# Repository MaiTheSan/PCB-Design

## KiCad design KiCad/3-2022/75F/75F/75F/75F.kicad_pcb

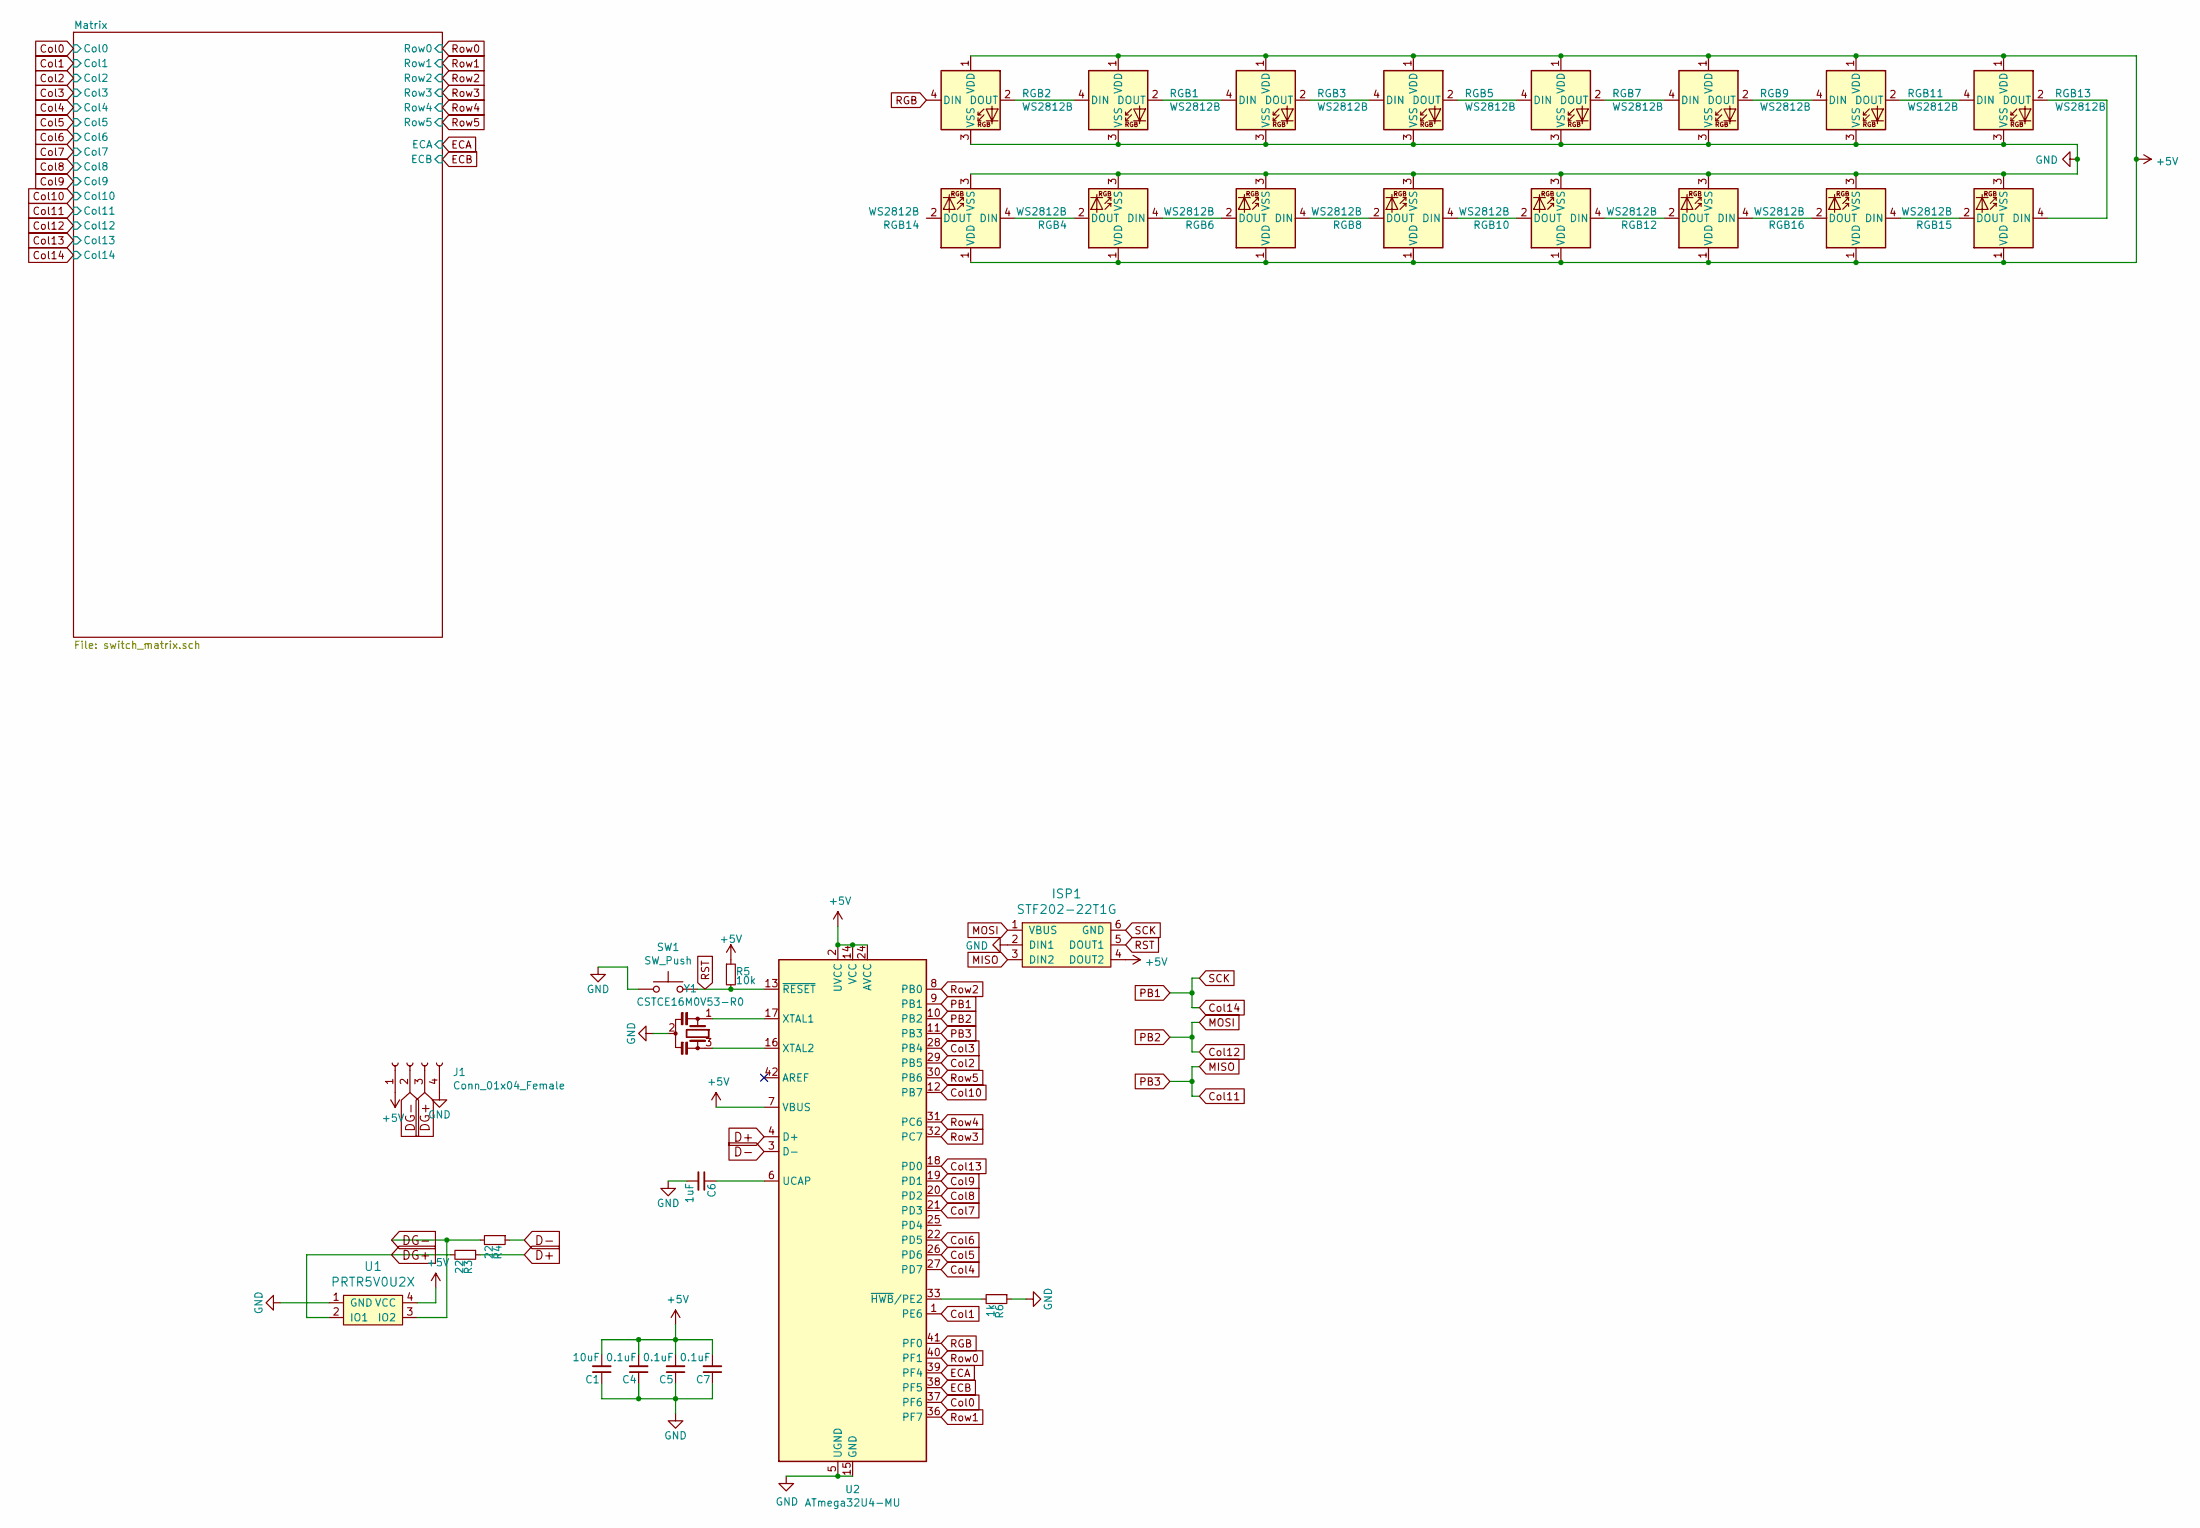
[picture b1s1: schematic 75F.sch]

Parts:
C1: 10uF; C_0603
C4, C5, C7: 0.1uF; C_0603
C6: 1uF; C_0603
ISP1: STF202-22T1G; Tag-Connect_TC2030-IDC-NL_2x03_P1.27mm_Vertical
J1: Conn_01x04_Female; JST-SR-4
R3, R4: 22; R_0805
R5: 10k; R_0805
R6: 1k; R_0805
RGB1, RGB2, RGB3, RGB4, RGB5, RGB6, RGB7, RGB8, RGB9, RGB10, RGB11, RGB12, RGB13, RGB15, RGB16: WS2812B; LED_WS2812B_PLCC4_5.0x5.0mm_P3.2mm
RGB14: WS2812B; RGB-6028_FLIPPED
SW1: SW_Push; SKQG-1155865
U1: PRTR5V0U2X; SOT143B
U2: ATmega32U4-MU; QFN-44-1EP_7x7mm_P0.5mm_EP5.15x5.15mm
Y1: CSTCE16M0V53-R0; Resonator_SMD_muRata_CSTxExxV-3Pin_3.0x1.1mm

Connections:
+5V: C1.2, C4.2, C5.2, C7.2, ISP1.4 (DOUT2), J1.1, R5.1, RGB1.1 (VDD), RGB2.1 (VDD), RGB3.1 (VDD), RGB4.1 (VDD), RGB5.1 (VDD), RGB6.1 (VDD), RGB7.1 (VDD), RGB8.1 (VDD), RGB9.1 (VDD), RGB10.1 (VDD), RGB11.1 (VDD), RGB12.1 (VDD), RGB13.1 (VDD), RGB14.1 (VDD), RGB15.1 (VDD), RGB16.1 (VDD), U1.4 (VCC), U2.2 (UVCC), U2.7 (VBUS), U2.14 (VCC), U2.24 (AVCC), U2.34 (VCC), U2.44 (AVCC); also elsewhere on the board
Col0: U2.37 (PF6); also elsewhere on the board
Col1: U2.1 (PE6); also elsewhere on the board
Col2: U2.29 (PB5); also elsewhere on the board
Col3: U2.28 (PB4); also elsewhere on the board
Col4: U2.27 (PD7); also elsewhere on the board
Col5: U2.26 (PD6); also elsewhere on the board
Col6: U2.22 (PD5); also elsewhere on the board
Col7: U2.21 (PD3); also elsewhere on the board
Col8: U2.20 (PD2); also elsewhere on the board
Col9: U2.19 (PD1); also elsewhere on the board
Col10: U2.12 (PB7); also elsewhere on the board
Col11: ISP1.3 (DIN2), U2.11 (PB3); also elsewhere on the board
Col12: ISP1.1 (VBUS), U2.10 (PB2); also elsewhere on the board
Col13: U2.18 (PD0); also elsewhere on the board
Col14: ISP1.6 (GND), U2.9 (PB1); also elsewhere on the board
D+: R3.1, U2.4 (D+)
D-: R4.1, U2.3 (D-)
DG+: J1.3, R3.2, U1.2 (IO1)
DG-: J1.2, R4.2, U1.3 (IO2)
ECA: U2.39 (PF4); also elsewhere on the board
ECB: U2.38 (PF5); also elsewhere on the board
GND: C1.1, C4.1, C5.1, C6.2, C7.1, ISP1.2 (DIN1), J1.4, R6.1, RGB1.3 (VSS), RGB2.3 (VSS), RGB3.3 (VSS), RGB4.3 (VSS), RGB5.3 (VSS), RGB6.3 (VSS), RGB7.3 (VSS), RGB8.3 (VSS), RGB9.3 (VSS), RGB10.3 (VSS), RGB11.3 (VSS), RGB12.3 (VSS), RGB13.3 (VSS), RGB14.3 (VSS), RGB15.3 (VSS), RGB16.3 (VSS), SW1.1, U1.1 (GND), U2.5 (UGND), U2.15 (GND), U2.23 (GND), U2.35 (GND), U2.43 (GND), U2.45 (GND), Y1.2; also elsewhere on the board
unnamed: C6.1, U2.6 (UCAP)
unnamed: R6.2, U2.33 (~HWB~/PE2)
unnamed: RGB1.2 (DOUT), RGB3.4 (DIN)
unnamed: RGB1.4 (DIN), RGB2.2 (DOUT)
unnamed: RGB3.2 (DOUT), RGB5.4 (DIN)
unnamed: RGB4.4 (DIN), RGB6.2 (DOUT)
unnamed: RGB5.2 (DOUT), RGB7.4 (DIN)
unnamed: RGB6.4 (DIN), RGB8.2 (DOUT)
unnamed: RGB7.2 (DOUT), RGB9.4 (DIN)
unnamed: RGB8.4 (DIN), RGB10.2 (DOUT)
unnamed: RGB10.4 (DIN), RGB12.2 (DOUT)
unnamed: RGB11.2 (DOUT), RGB13.4 (DIN)
unnamed: RGB9.2 (DOUT), RGB11.4 (DIN)
unnamed: RGB12.4 (DIN), RGB16.2 (DOUT)
unnamed: RGB13.2 (DOUT), RGB15.4 (DIN)
unnamed: RGB4.2 (DOUT), RGB14.4 (DIN)
unnamed: RGB15.2 (DOUT), RGB16.4 (DIN)
unnamed: U2.16 (XTAL2), Y1.3
unnamed: U2.17 (XTAL1), Y1.1
RGB: RGB2.4 (DIN), U2.41 (PF0)
RST: ISP1.5 (DOUT1), R5.2, SW1.2, U2.13 (~RESET)
Row0: U2.40 (PF1); also elsewhere on the board
Row1: U2.36 (PF7); also elsewhere on the board
Row2: U2.8 (PB0); also elsewhere on the board
Row3: U2.32 (PC7); also elsewhere on the board
Row4: U2.31 (PC6); also elsewhere on the board
Row5: U2.30 (PB6); also elsewhere on the board

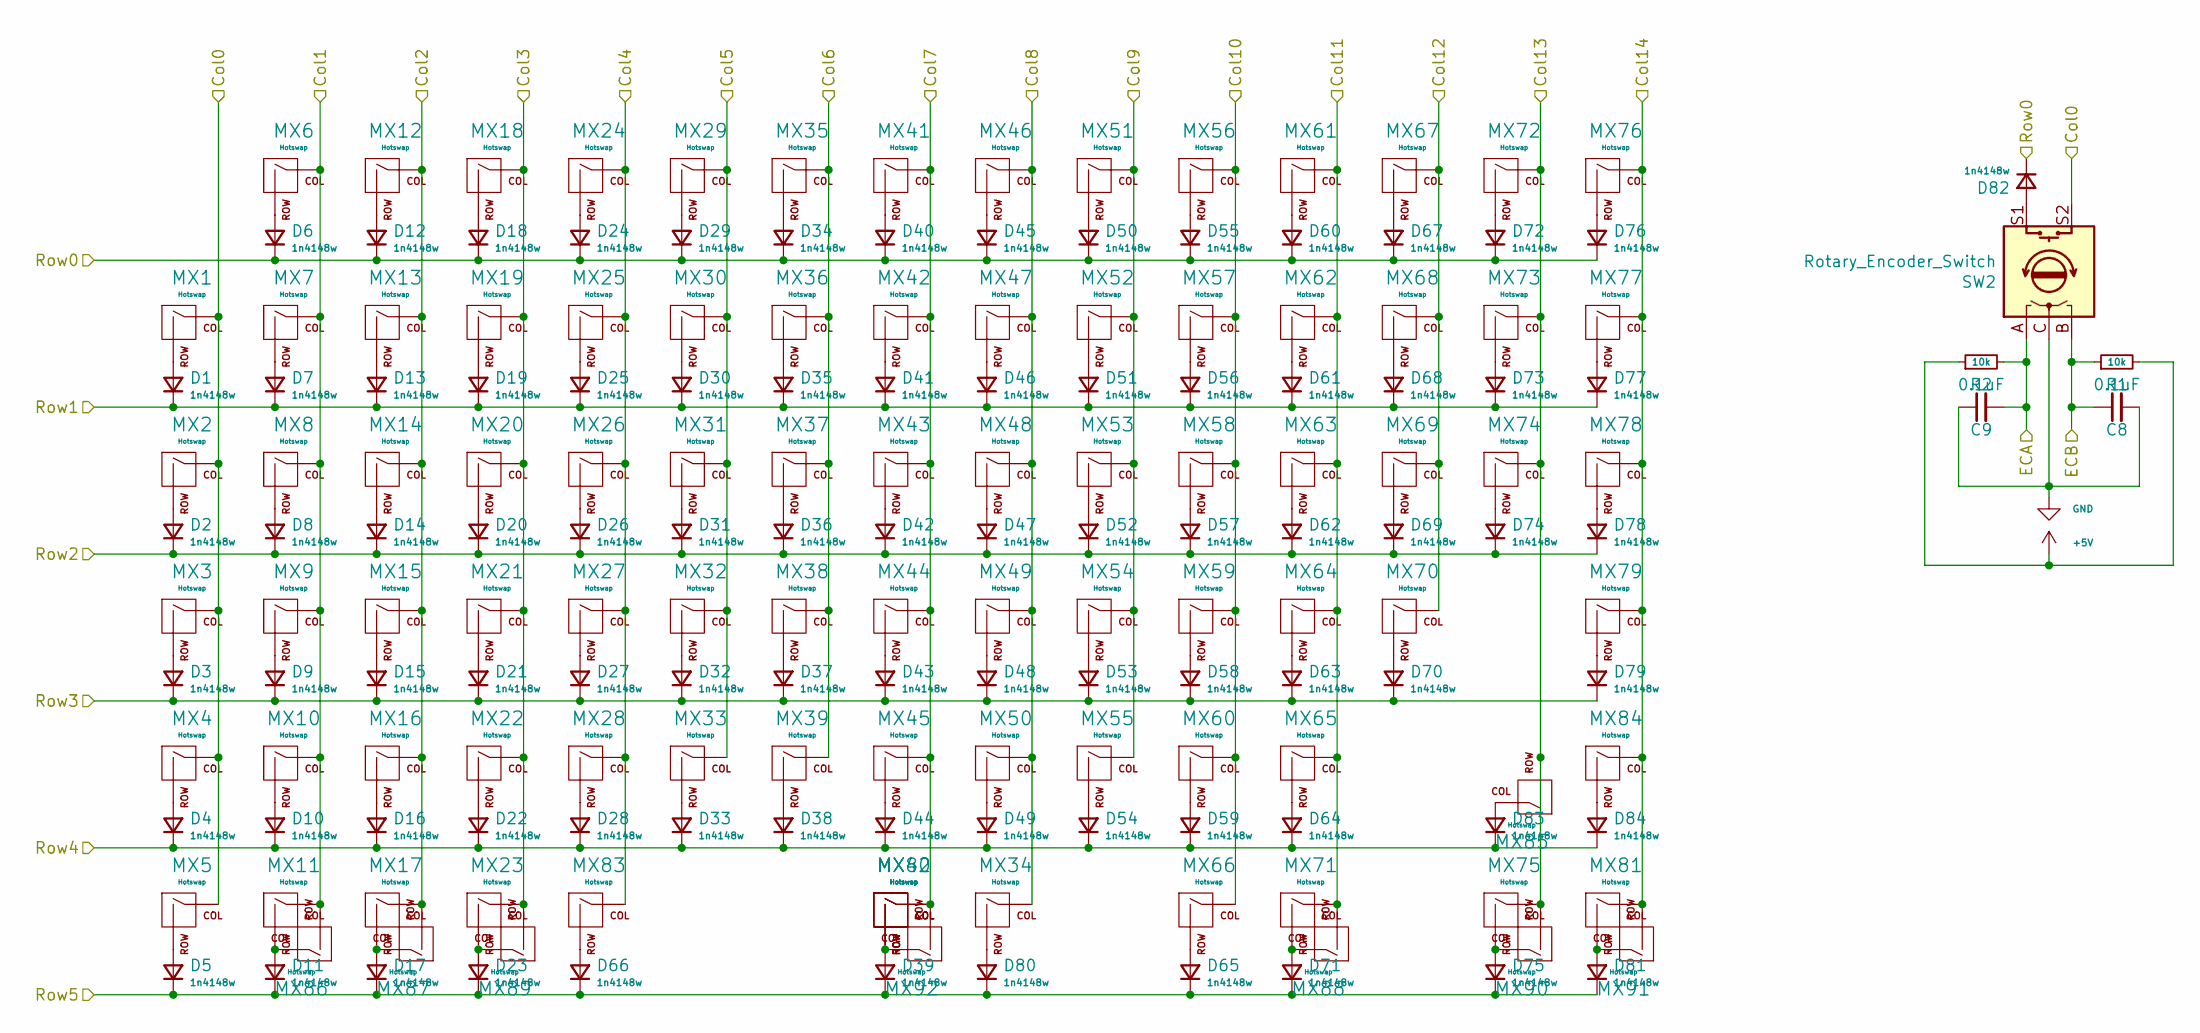
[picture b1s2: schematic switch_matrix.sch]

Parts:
C8, C9: 0.1uF; C_0603
D1, D2, D3, D4, D5, D6, D7, D8, D9, D10, D11, D12, D13, D14, D15, D16, D17, D18, D19, D20, D21, D22, D23, D24, D25, D26, D27, D28, D29, D30, D31, D32, D33, D34, D35, D36, D37, D38, D39, D40, D41, D42, D43, D44, D45, D46, D47, D48, D49, D50, D51, D52, D53, D54, D55, D56, D57, D58, D59, D60, D61, D62, D63, D64, D65, D66, D67, D68, D69, D70, D71, D72, D73, D74, D75, D76, D77, D78, D79, D80, D81, D82, D83, D84: 1n4148w; DIODE_1206_SawnsProjects
MX1, MX2, MX3, MX4, MX5, MX6, MX7, MX12, MX13, MX14, MX15, MX16, MX18, MX19, MX20, MX21, MX22, MX24, MX25, MX26, MX27, MX28, MX29, MX30, MX31, MX32, MX33, MX35, MX36, MX37, MX38, MX39, MX41, MX42, MX43, MX44, MX45, MX46, MX47, MX48, MX49, MX50, MX51, MX52, MX53, MX54, MX55, MX56, MX57, MX58, MX59, MX60, MX61, MX62, MX63, MX64, MX65, MX67, MX68, MX69, MX70, MX72, MX73, MX74, MX76, MX84, MX87, MX90: Hotswap; MXOnly-1U-Hotswap-Sawns
MX8, MX78, MX86, MX88, MX89, MX91: Hotswap; MXOnly-1.5U-Hotswap-Sawns
MX9, MX85: Hotswap; MXOnly-1.75U-Hotswap-Sawns
MX10, MX82: Hotswap; MXOnly-2.25U-Hotswap-Sawns
MX11, MX17, MX23, MX66, MX71, MX75, MX81, MX83: Hotswap; MXOnly-1.25U-Hotswap-Sawns
MX34: Hotswap; MXOnly-2.75U-Hotswap-ReversedStabilizers-Sawns
MX40: Hotswap; MXOnly-6.25U-Hotswap-ReversedStabilizers-Sawns
MX77: Hotswap; MXOnly-2U-Hotswap-Sawns
MX79: Hotswap; MXOnly-2.25U-Hotswap-ReversedStabilizers-Sawns
MX92: Hotswap; MXOnly-7U-Hotswap-Sawns
R1, R2: 10k; R_0805
SW2: Rotary_Encoder_Switch; RotaryEncoder_Alps_EC11E-Switch_Vertical_H20mm_Center

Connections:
+5V: R1.2, R2.1; also elsewhere on the board
Col0: MX1.1 (COL), MX2.1 (COL), MX3.1 (COL), MX4.1 (COL), MX5.1 (COL), SW2.S2; also elsewhere on the board
Col1: MX6.1 (COL), MX7.1 (COL), MX8.1 (COL), MX9.1 (COL), MX10.1 (COL), MX11.1 (COL), MX86.2 (ROW); also elsewhere on the board
Col2: MX12.1 (COL), MX13.1 (COL), MX14.1 (COL), MX15.1 (COL), MX16.1 (COL), MX17.1 (COL), MX87.2 (ROW); also elsewhere on the board
Col3: MX18.1 (COL), MX19.1 (COL), MX20.1 (COL), MX21.1 (COL), MX22.1 (COL), MX23.1 (COL), MX89.2 (ROW); also elsewhere on the board
Col4: MX24.1 (COL), MX25.1 (COL), MX26.1 (COL), MX27.1 (COL), MX28.1 (COL), MX83.1 (COL); also elsewhere on the board
Col5: MX29.1 (COL), MX30.1 (COL), MX31.1 (COL), MX32.1 (COL), MX33.1 (COL); also elsewhere on the board
Col6: MX35.1 (COL), MX36.1 (COL), MX37.1 (COL), MX38.1 (COL), MX39.1 (COL); also elsewhere on the board
Col7: MX40.1 (COL), MX41.1 (COL), MX42.1 (COL), MX43.1 (COL), MX44.1 (COL), MX45.1 (COL), MX82.1 (COL), MX92.2 (ROW); also elsewhere on the board
Col8: MX34.1 (COL), MX46.1 (COL), MX47.1 (COL), MX48.1 (COL), MX49.1 (COL), MX50.1 (COL); also elsewhere on the board
Col9: MX51.1 (COL), MX52.1 (COL), MX53.1 (COL), MX54.1 (COL), MX55.1 (COL); also elsewhere on the board
Col10: MX56.1 (COL), MX57.1 (COL), MX58.1 (COL), MX59.1 (COL), MX60.1 (COL), MX66.1 (COL); also elsewhere on the board
Col11: MX61.1 (COL), MX62.1 (COL), MX63.1 (COL), MX64.1 (COL), MX65.1 (COL), MX71.1 (COL), MX88.2 (ROW); also elsewhere on the board
Col12: MX67.1 (COL), MX68.1 (COL), MX69.1 (COL), MX70.1 (COL); also elsewhere on the board
Col13: MX72.1 (COL), MX73.1 (COL), MX74.1 (COL), MX75.1 (COL), MX85.2 (ROW), MX90.2 (ROW); also elsewhere on the board
Col14: MX76.1 (COL), MX77.1 (COL), MX78.1 (COL), MX79.1 (COL), MX81.1 (COL), MX84.1 (COL), MX91.2 (ROW); also elsewhere on the board
ECA: C9.2, R2.2, SW2.A; also elsewhere on the board
ECB: C8.1, R1.1, SW2.B; also elsewhere on the board
GND: C8.2, C9.1, SW2.C; also elsewhere on the board
unnamed: D1.2 (A), MX1.2 (ROW)
unnamed: D2.2 (A), MX2.2 (ROW)
unnamed: D3.2 (A), MX3.2 (ROW)
unnamed: D4.2 (A), MX4.2 (ROW)
unnamed: D5.2 (A), MX5.2 (ROW)
unnamed: D6.2 (A), MX6.2 (ROW)
unnamed: D7.2 (A), MX7.2 (ROW)
unnamed: D8.2 (A), MX8.2 (ROW)
unnamed: D9.2 (A), MX9.2 (ROW)
unnamed: D10.2 (A), MX10.2 (ROW)
unnamed: D11.2 (A), MX11.2 (ROW), MX86.1 (COL)
unnamed: D12.2 (A), MX12.2 (ROW)
unnamed: D13.2 (A), MX13.2 (ROW)
unnamed: D14.2 (A), MX14.2 (ROW)
unnamed: D15.2 (A), MX15.2 (ROW)
unnamed: D16.2 (A), MX16.2 (ROW)
unnamed: D17.2 (A), MX17.2 (ROW), MX87.1 (COL)
unnamed: D18.2 (A), MX18.2 (ROW)
unnamed: D19.2 (A), MX19.2 (ROW)
unnamed: D20.2 (A), MX20.2 (ROW)
unnamed: D21.2 (A), MX21.2 (ROW)
unnamed: D22.2 (A), MX22.2 (ROW)
unnamed: D23.2 (A), MX23.2 (ROW), MX89.1 (COL)
unnamed: D24.2 (A), MX24.2 (ROW)
unnamed: D25.2 (A), MX25.2 (ROW)
unnamed: D26.2 (A), MX26.2 (ROW)
unnamed: D27.2 (A), MX27.2 (ROW)
unnamed: D28.2 (A), MX28.2 (ROW)
unnamed: D29.2 (A), MX29.2 (ROW)
unnamed: D30.2 (A), MX30.2 (ROW)
unnamed: D31.2 (A), MX31.2 (ROW)
unnamed: D32.2 (A), MX32.2 (ROW)
unnamed: D33.2 (A), MX33.2 (ROW)
unnamed: D34.2 (A), MX35.2 (ROW)
unnamed: D35.2 (A), MX36.2 (ROW)
unnamed: D36.2 (A), MX37.2 (ROW)
unnamed: D37.2 (A), MX38.2 (ROW)
unnamed: D38.2 (A), MX39.2 (ROW)
unnamed: D39.2 (A), MX40.2 (ROW), MX82.2 (ROW), MX92.1 (COL)
unnamed: D40.2 (A), MX41.2 (ROW)
unnamed: D41.2 (A), MX42.2 (ROW)
unnamed: D42.2 (A), MX43.2 (ROW)
unnamed: D43.2 (A), MX44.2 (ROW)
unnamed: D44.2 (A), MX45.2 (ROW)
unnamed: D45.2 (A), MX46.2 (ROW)
unnamed: D46.2 (A), MX47.2 (ROW)
unnamed: D47.2 (A), MX48.2 (ROW)
unnamed: D48.2 (A), MX49.2 (ROW)
unnamed: D49.2 (A), MX50.2 (ROW)
unnamed: D50.2 (A), MX51.2 (ROW)
unnamed: D51.2 (A), MX52.2 (ROW)
unnamed: D52.2 (A), MX53.2 (ROW)
unnamed: D53.2 (A), MX54.2 (ROW)
unnamed: D54.2 (A), MX55.2 (ROW)
unnamed: D55.2 (A), MX56.2 (ROW)
unnamed: D56.2 (A), MX57.2 (ROW)
unnamed: D57.2 (A), MX58.2 (ROW)
unnamed: D58.2 (A), MX59.2 (ROW)
unnamed: D59.2 (A), MX60.2 (ROW)
unnamed: D60.2 (A), MX61.2 (ROW)
unnamed: D61.2 (A), MX62.2 (ROW)
unnamed: D62.2 (A), MX63.2 (ROW)
unnamed: D63.2 (A), MX64.2 (ROW)
unnamed: D64.2 (A), MX65.2 (ROW)
unnamed: D65.2 (A), MX66.2 (ROW)
unnamed: D66.2 (A), MX83.2 (ROW)
unnamed: D67.2 (A), MX67.2 (ROW)
unnamed: D68.2 (A), MX68.2 (ROW)
unnamed: D69.2 (A), MX69.2 (ROW)
unnamed: D70.2 (A), MX70.2 (ROW)
unnamed: D71.2 (A), MX71.2 (ROW), MX88.1 (COL)
unnamed: D72.2 (A), MX72.2 (ROW)
unnamed: D73.2 (A), MX73.2 (ROW)
unnamed: D74.2 (A), MX74.2 (ROW)
unnamed: D75.2 (A), MX75.2 (ROW), MX90.1 (COL)
unnamed: D76.2 (A), MX76.2 (ROW)
unnamed: D77.2 (A), MX77.2 (ROW)
unnamed: D78.2 (A), MX78.2 (ROW)
unnamed: D79.2 (A), MX79.2 (ROW)
unnamed: D80.2 (A), MX34.2 (ROW)
unnamed: D81.2 (A), MX81.2 (ROW), MX91.1 (COL)
unnamed: D82.2 (A), SW2.S1
unnamed: D83.2 (A), MX85.1 (COL)
unnamed: D84.2 (A), MX84.2 (ROW)
Row0: D6.1 (K), D12.1 (K), D18.1 (K), D24.1 (K), D29.1 (K), D34.1 (K), D40.1 (K), D45.1 (K), D50.1 (K), D55.1 (K), D60.1 (K), D67.1 (K), D72.1 (K), D76.1 (K), D82.1 (K); also elsewhere on the board
Row1: D1.1 (K), D7.1 (K), D13.1 (K), D19.1 (K), D25.1 (K), D30.1 (K), D35.1 (K), D41.1 (K), D46.1 (K), D51.1 (K), D56.1 (K), D61.1 (K), D68.1 (K), D73.1 (K), D77.1 (K); also elsewhere on the board
Row2: D2.1 (K), D8.1 (K), D14.1 (K), D20.1 (K), D26.1 (K), D31.1 (K), D36.1 (K), D42.1 (K), D47.1 (K), D52.1 (K), D57.1 (K), D62.1 (K), D69.1 (K), D74.1 (K), D78.1 (K); also elsewhere on the board
Row3: D3.1 (K), D9.1 (K), D15.1 (K), D21.1 (K), D27.1 (K), D32.1 (K), D37.1 (K), D43.1 (K), D48.1 (K), D53.1 (K), D58.1 (K), D63.1 (K), D70.1 (K), D79.1 (K); also elsewhere on the board
Row4: D4.1 (K), D10.1 (K), D16.1 (K), D22.1 (K), D28.1 (K), D33.1 (K), D38.1 (K), D44.1 (K), D49.1 (K), D54.1 (K), D59.1 (K), D64.1 (K), D83.1 (K), D84.1 (K); also elsewhere on the board
Row5: D5.1 (K), D11.1 (K), D17.1 (K), D23.1 (K), D39.1 (K), D65.1 (K), D66.1 (K), D71.1 (K), D75.1 (K), D80.1 (K), D81.1 (K); also elsewhere on the board

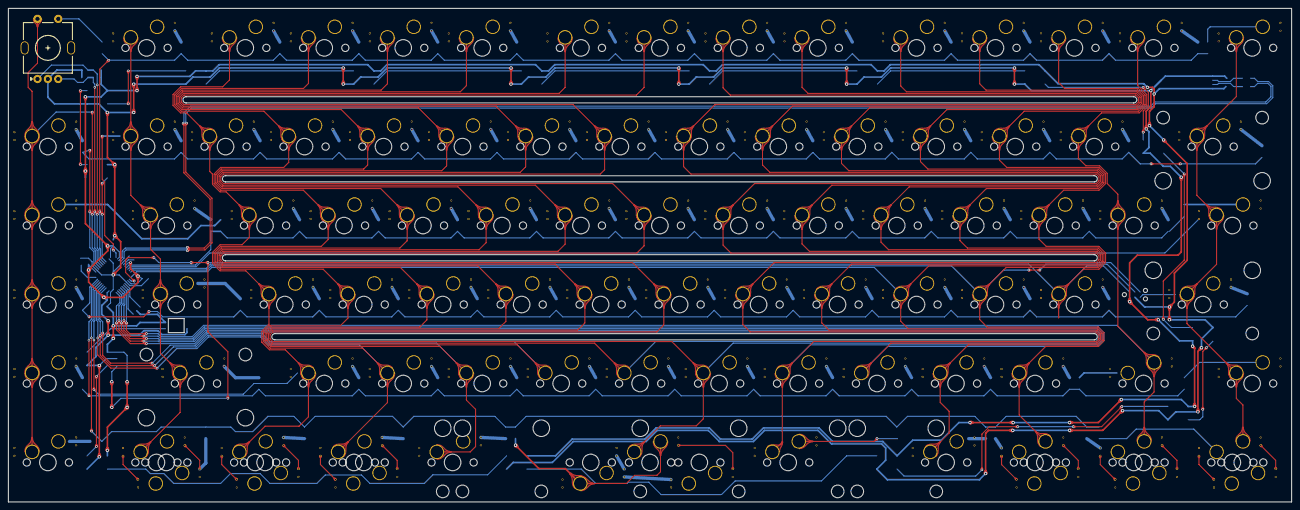
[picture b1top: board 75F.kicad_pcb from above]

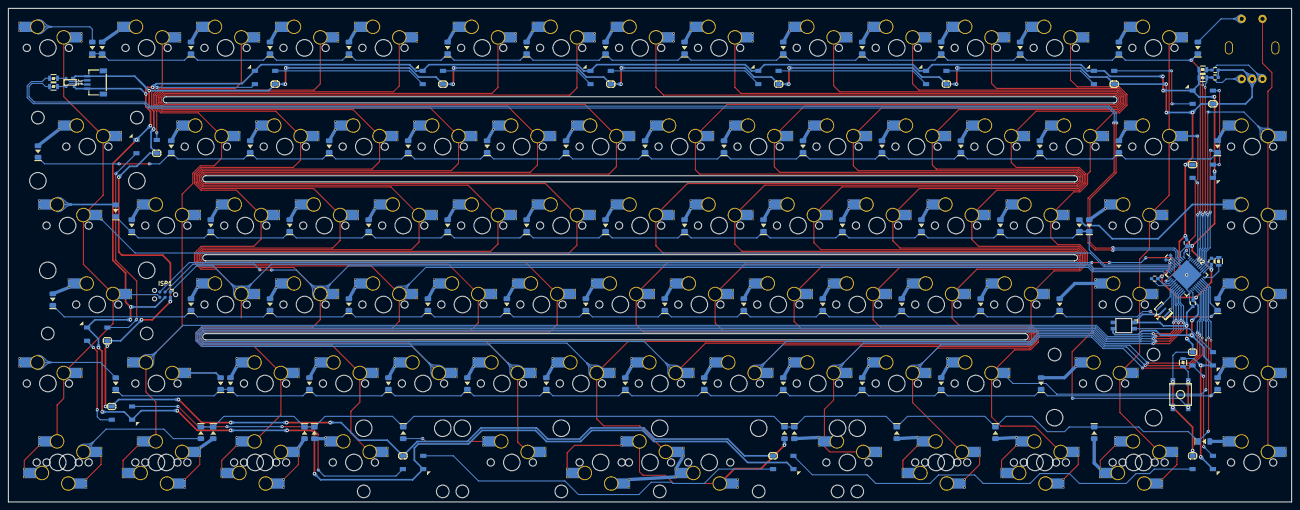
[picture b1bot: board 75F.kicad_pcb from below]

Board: 2 copper layers, 309.6 x 119.1 mm, 211 parts (119 on the bottom side), 134 nets.

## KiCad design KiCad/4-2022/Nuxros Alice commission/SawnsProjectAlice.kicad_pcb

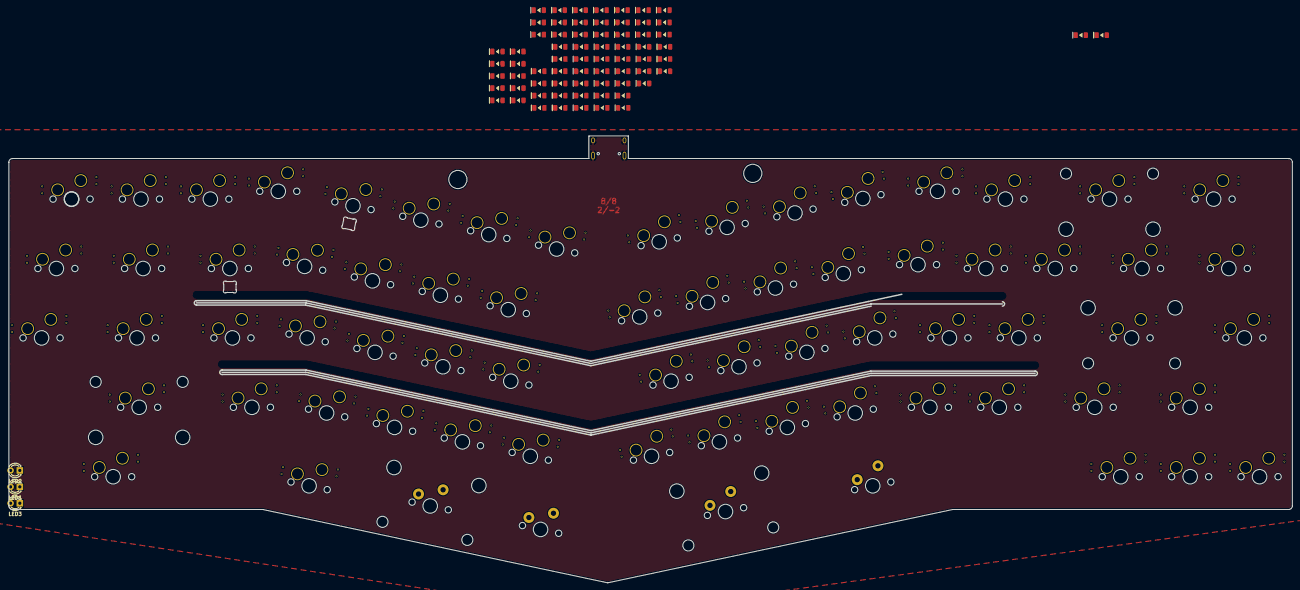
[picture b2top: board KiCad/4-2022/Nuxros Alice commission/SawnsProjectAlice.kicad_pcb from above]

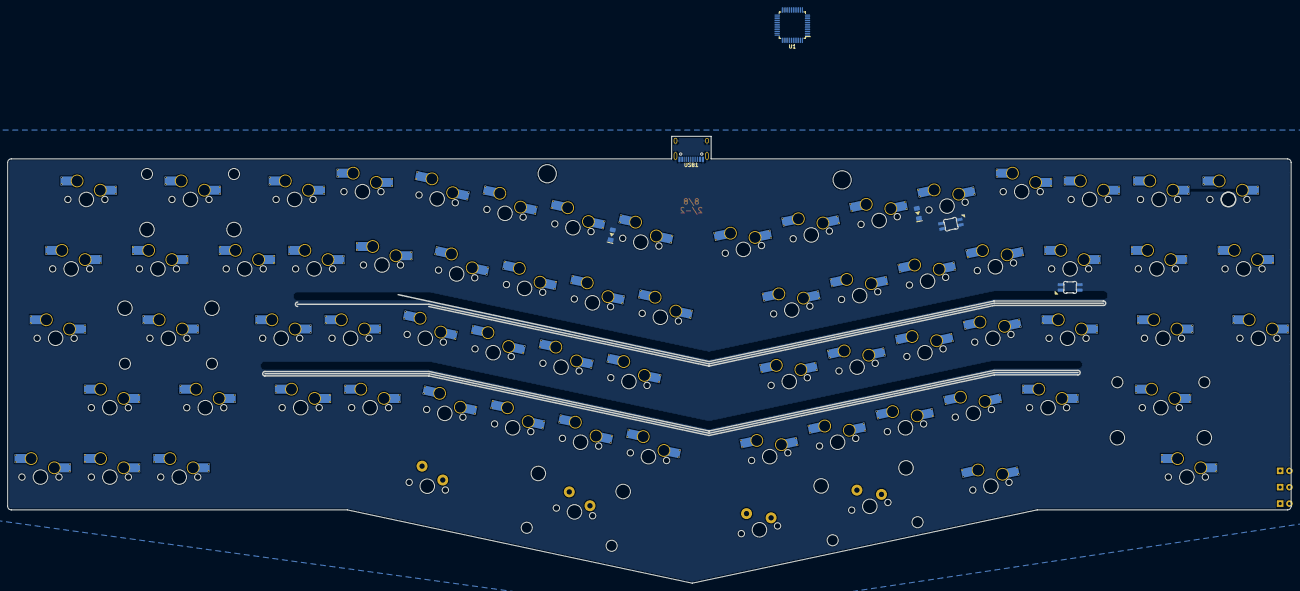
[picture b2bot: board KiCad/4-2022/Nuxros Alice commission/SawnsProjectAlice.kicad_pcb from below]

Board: 2 copper layers, 352.3 x 122.6 mm, 147 parts (4 on the bottom side), 91 nets, no tracks yet.

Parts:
D1, D2, D3, D4, D5, D6, D7, D8, D9, D10, D11, D12, D13, D14, D15, D16, D17, D18, D19, D20, D21, D22, D23, D24, D25, D26, D27, D28, D29, D30, D31, D32, D33, D34, D35, D36, D37, D38, D39, D40, D41, D42, D43, D44, D45, D46, D47, D48, D49, D50, D51, D52, D53, D54, D55, D56, D57, D58, D59, D60, D61, D62, D63, D64, D65, D66, D67, D68, D69, D70: SOD_123; DIODE_1206_SawnsProjects
K_0, K_1, K_2, K_3, K_4, K_5, K_6, K_7, K_8, K_9, K_.1: 1U; MXOnly-1U-Hotswap-Sawns
K_'1: 1U; MXOnly-1U-Hotswap-Sawns
K_+1: 1U; MXOnly-1U-Hotswap-Sawns
K_,1: 1U; MXOnly-1U-Hotswap-Sawns
K_-_1: 1U; MXOnly-1U-Hotswap-Sawns
K_/?/1: 1U; MXOnly-1U-Hotswap-Sawns
K_;1: 1U; MXOnly-1U-Hotswap-Sawns
K_A1: 1U; MXOnly-1U-Hotswap-Sawns
K_Alt1: 1.25U; MXOnly-1.25U-Hotswap-Sawns
K_B1: 1U; MXOnly-1U-Hotswap-Sawns
K_BkSp2: 2U_FL; MXOnly-2U-Hotswap-Sawns
K_C1: 1U; MXOnly-1U-Hotswap-Sawns
K_CapLk1: MX-1U-MX_Alps_Hybrids; MXOnly-1.75U-Hotswap-Sawns
K_D1: 1U; MXOnly-1U-Hotswap-Sawns
K_DEL1: 1U; MXOnly-1U-Hotswap-Sawns
K_DOWN1: 1U; MXOnly-1U-Hotswap-Sawns
K_Delete1: 1U; MXOnly-1U-Hotswap-Sawns
K_E1: 1U; MXOnly-1U-Hotswap-Sawns
K_ESC1: 1U; MXOnly-1U-Hotswap-Sawns
K_Enter1: 2.25U; MXOnly-2.25U-Hotswap-ReversedStabilizers-Sawns
K_F1: 1U; MXOnly-1U-Hotswap-Sawns
K_G1: 1U; MXOnly-1U-Hotswap-Sawns
K_H1: 1U; MXOnly-1U-Hotswap-Sawns
K_I1: 1U; MXOnly-1U-Hotswap-Sawns
K_J1: 1U; MXOnly-1U-Hotswap-Sawns
K_K1: 1U; MXOnly-1U-Hotswap-Sawns
K_L1: 1U; MXOnly-1U-Hotswap-Sawns
K_LControl1: 1.5U; MXOnly-1.5U-Hotswap-Sawns
K_LEFT1: 1U; MXOnly-1U-Hotswap-Sawns
K_LShift1: MX-1U-MX_Alps_Hybrids; MXOnly-2.25U-Hotswap-Sawns
K_M1: 1U; MXOnly-1U-Hotswap-Sawns
K_N1: 1U; MXOnly-1U-Hotswap-Sawns
K_O1: 1U; MXOnly-1U-Hotswap-Sawns
K_P1: 1U; MXOnly-1U-Hotswap-Sawns
K_PRTSC1: 1U; MXOnly-1U-Hotswap-Sawns
K_PgDn1: 1U; MXOnly-1U-Hotswap-Sawns
K_PgUp1: 1U; MXOnly-1U-Hotswap-Sawns
K_Q1: 1U; MXOnly-1U-Hotswap-Sawns
K_R1: 1U; MXOnly-1U-Hotswap-Sawns
K_RIGHT1: 1U; MXOnly-1U-Hotswap-Sawns
K_RSHIFT3: 1U; MXOnly-1U-Hotswap-Sawns
K_RShift1: 1.75U; MXOnly-1.75U-Hotswap-Sawns
K_S1: 1U; MXOnly-1U-Hotswap-Sawns
K_T1: 1U; MXOnly-1U-Hotswap-Sawns
K_Tab1: 1.5U; MXOnly-1.5U-Hotswap-Sawns
K_U1: 1U; MXOnly-1U-Hotswap-Sawns
K_UP1: 1U; MXOnly-1U-Hotswap-Sawns
K_V1: 1U; MXOnly-1U-Hotswap-Sawns
K_W1: 1U; MXOnly-1U-Hotswap-Sawns
K_X1: 1U; MXOnly-1U-Hotswap-Sawns
K_Y1: 1U; MXOnly-1U-Hotswap-Sawns
K_Z1: 1U; MXOnly-1U-Hotswap-Sawns
K_]}1: 1U; MXOnly-1U-Hotswap-Sawns
K_`1: 1U; MXOnly-1U-Hotswap-Sawns
K_{[1: 1U; MXOnly-1U-Hotswap-Sawns
K_|\1: 1.5U; MXOnly-1.5U-Hotswap-Sawns
LED1, LED2, LED3: LED; LED_D3.0mm
MX1: 2U; MXOnly-2U-ReversedStabilizers-NoLED
MX2, MX4: MX-1U-MX_Alps_Hybrids; MXOnly-1U-NoLED
MX3: 2.75U; MXOnly-2.75U-ReversedStabilizers-NoLED
RGB1: SK6812_Mini_E; MX_SK6812MINI-E_REV
RGB_RV1: SK6812_Mini_E; MX_SK6812MINI-E
U1: STM32F072CBTx; LQFP-48_7x7mm_P0.5mm
USB1: HRO-TYPE-C-31-M-12; HRO-TYPE-C-31-M-12-Assembly

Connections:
+5V: LED1.2, LED2.2, LED3.2, USB1.2, USB1.11
GND: USB1.1, USB1.12, USB1.13
unnamed: D1.1, D10.1, D11.1, D20.1, D36.1, D45.1, D54.1, D62.1
unnamed: D1.2, K_ESC1.2
unnamed: D2.2, K_`1.2
unnamed: D3.2, K_PgUp1.2
unnamed: D4.2, K_PgDn1.2
unnamed: D5.2, K_2.2
unnamed: D6.2, K_Tab1.2
unnamed: D7.2, K_CapLk1.2
unnamed: D8.2, K_LShift1.2
unnamed: D9.2, K_LControl1.2
unnamed: D10.2, K_3.2
unnamed: D11.2, K_1.2
unnamed: D3.1, D12.1, D21.1, D28.1, D37.1, D46.1, D55.1, D63.1
unnamed: D12.2, K_Q1.2
unnamed: D4.1, D13.1, D22.1, D29.1, D38.1, D47.1, D56.1, D64.1
unnamed: D13.2, K_A1.2
unnamed: D14.1, D23.1, D30.1, D39.1, D48.1, D57.1
unnamed: D14.2, K_Z1.2
unnamed: D2.1, D5.1, D15.1, D31.1, D40.1, D49.1, D58.1, D66.1
unnamed: D15.2, K_4.2
unnamed: D6.1, D16.1, D24.1, D32.1, D41.1, D50.1, D59.1, D69.1
unnamed: D16.2, K_W1.2
unnamed: D7.1, D17.1, D25.1, D33.1, D42.1, D51.1, D70.1
unnamed: D17.2, K_S1.2
unnamed: D8.1, D18.1, D26.1, D34.1, D43.1, D52.1, D60.1, D67.1
unnamed: D18.2, K_X1.2
unnamed: D9.1, D19.1, D27.1, D35.1, D44.1, D53.1, D61.1, D68.1
unnamed: D19.2, K_Alt1.2
unnamed: D20.2, K_5.2
unnamed: D21.2, K_E1.2
unnamed: D22.2, K_D1.2
unnamed: D23.2, K_C1.2
unnamed: D24.2, K_R1.2
unnamed: D25.2, K_F1.2
unnamed: D26.2, K_V1.2
unnamed: D27.2, MX1.2
unnamed: D28.2, K_T1.2
unnamed: D29.2, K_G1.2
unnamed: D30.2, K_B1.2
unnamed: D31.2, K_6.2
unnamed: D32.2, K_Y1.2
unnamed: D33.2, K_H1.2
unnamed: D34.2, K_N1.2
unnamed: D35.2, MX2.2
unnamed: D36.2, K_7.2
unnamed: D37.2, K_U1.2
unnamed: D38.2, K_J1.2
unnamed: D39.2, K_M1.2
unnamed: D40.2, K_8.2
unnamed: D41.2, K_I1.2
unnamed: D42.2, K_K1.2
unnamed: D43.2, K_,1.2
unnamed: D44.2, MX3.2
unnamed: D45.2, K_9.2
unnamed: D46.2, K_O1.2
unnamed: D47.2, K_L1.2
unnamed: D48.2, K_.1.2
unnamed: D49.2, K_0.2
unnamed: D50.2, K_P1.2
unnamed: D51.2, K_;1.2
unnamed: D52.2, K_/?/1.2
unnamed: D53.2, MX4.2
unnamed: D54.2, K_-_1.2
unnamed: D55.2, K_{[1.2
unnamed: D56.2, K_'1.2
unnamed: D57.2, K_RSHIFT3.2
unnamed: D58.2, K_+1.2
unnamed: D59.2, K_]}1.2
unnamed: D60.2, K_RShift1.2
unnamed: D61.2, K_DOWN1.2
unnamed: D62.2, K_BkSp2.2
unnamed: D63.2, K_|\1.2
unnamed: D64.2, K_Enter1.2
unnamed: D65.2, K_UP1.2
unnamed: D66.2, K_Delete1.2
unnamed: D67.2, K_RIGHT1.2
unnamed: D68.2, K_LEFT1.2
unnamed: D69.2, K_DEL1.2
unnamed: D70.2, K_PRTSC1.2
unnamed: K_1.1, K_2.1, K_A1.1, K_Alt1.1, K_Q1.1, K_S1.1, K_W1.1, K_X1.1, K_Z1.1
unnamed: K_3.1, K_4.1, K_C1.1, K_D1.1, K_E1.1, K_F1.1, K_R1.1, K_V1.1, MX1.1
unnamed: K_5.1, K_6.1, K_B1.1, K_G1.1, K_H1.1, K_N1.1, K_T1.1, K_Y1.1, MX2.1
unnamed: K_'1.1, K_+1.1, K_-_1.1, K_DOWN1.1, K_RSHIFT3.1, K_RShift1.1, K_]}1.1, K_{[1.1
unnamed: K_7.1, K_8.1, K_,1.1, K_I1.1, K_J1.1, K_K1.1, K_M1.1, K_U1.1, MX3.1
unnamed: K_0.1, K_9.1, K_.1.1, K_/?/1.1, K_;1.1, K_L1.1, K_O1.1, K_P1.1, MX4.1
unnamed: K_BkSp2.1, K_DEL1.1, K_Delete1.1, K_Enter1.1, K_LEFT1.1, K_PRTSC1.1, K_RIGHT1.1, K_UP1.1, K_|\1.1
unnamed: K_CapLk1.1, K_ESC1.1, K_LControl1.1, K_LShift1.1, K_PgDn1.1, K_PgUp1.1, K_Tab1.1, K_`1.1
unnamed: USB1.5, USB1.7
unnamed: USB1.6, USB1.8
